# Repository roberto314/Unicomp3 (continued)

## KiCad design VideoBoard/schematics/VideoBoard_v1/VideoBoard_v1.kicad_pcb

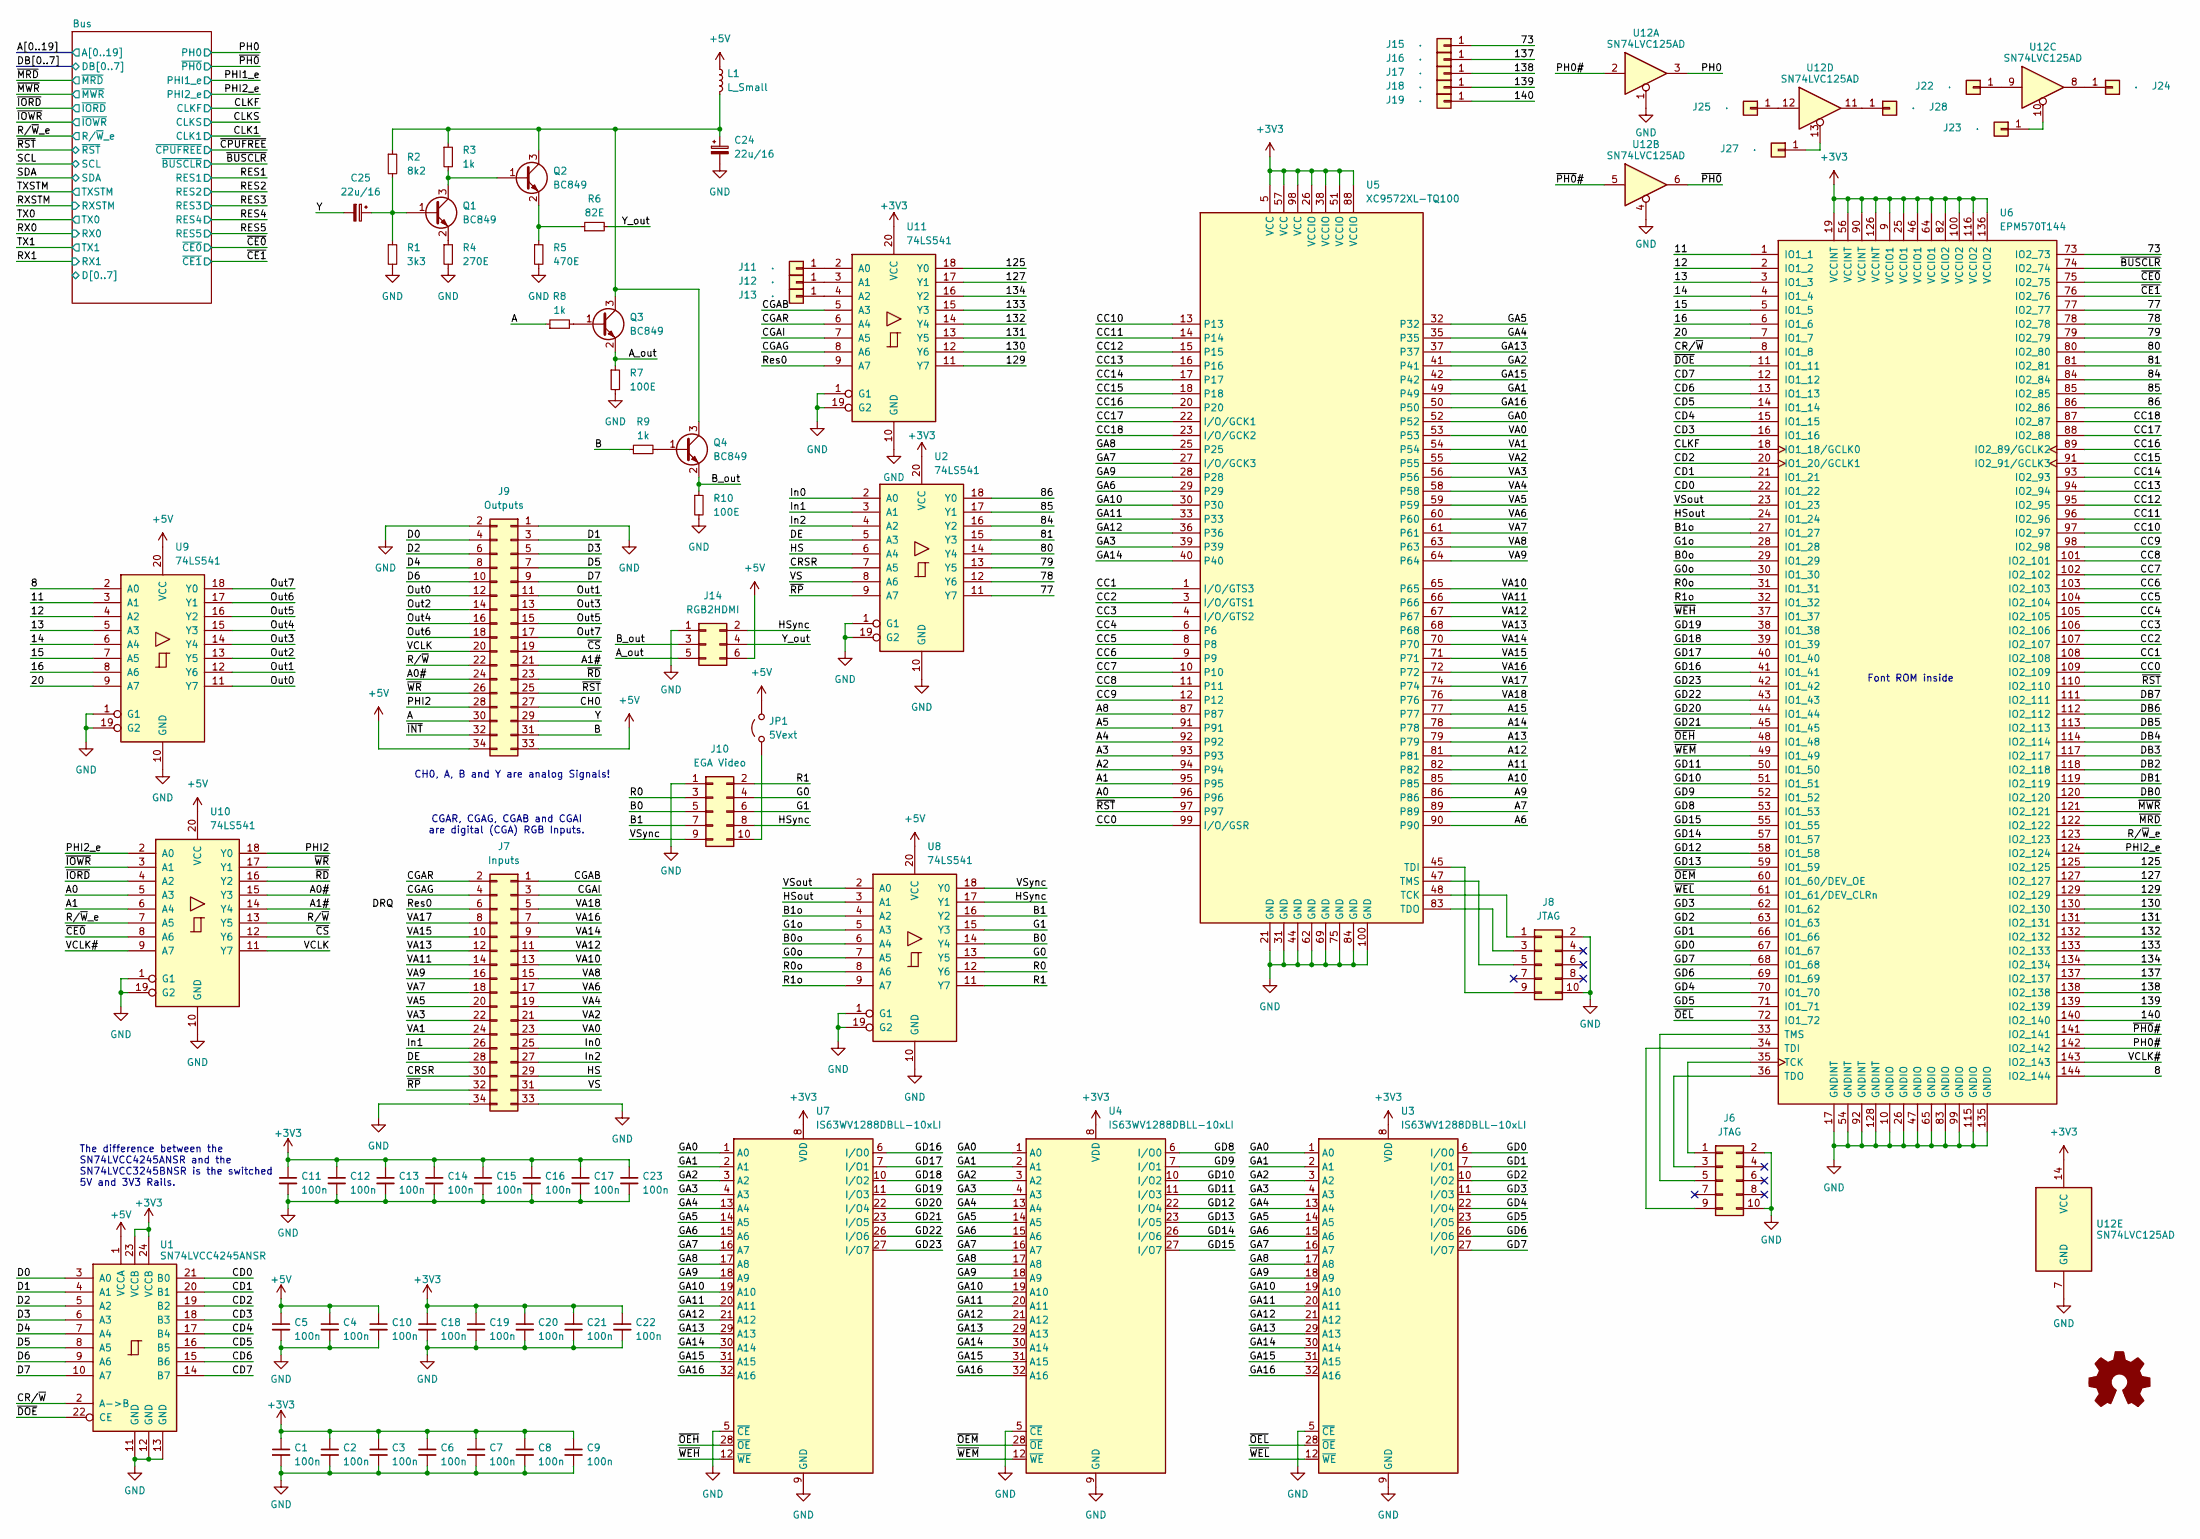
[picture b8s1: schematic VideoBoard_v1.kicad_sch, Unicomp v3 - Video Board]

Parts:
C1, C2, C3, C4, C5, C6, C7, C8, C9, C10, C11, C12, C13, C14, C15, C16, C17, C18, C19, C20, C21, C22, C23: 100n; C_0603_1608Metric_Pad1.08x0.95mm_HandSolder
C24, C25: 22u/16; CP_EIA-7343-31_Kemet-D
J6, J8: JTAG; PinHeader_2x05_P2.54mm_Horizontal
J7: Inputs; PinSocket_2x17_P2.54mm_Vertical
J9: Outputs; PinSocket_2x17_P2.54mm_Vertical
J10: EGA Video; PinHeader_2x05_P2.54mm_Horizontal
J11, J12, J13, J15, J16, J17, J18, J19, J22, J23, J24, J25, J27, J28: .; PinHeader_1x01_P1.27mm_Vertical
J14: RGB2HDMI; PinHeader_2x03_P2.54mm_Horizontal
JP1: 5Vext; PinHeader_1x02_P2.54mm_Vertical
L1: L_Small; L_1210_3225Metric_Pad1.42x2.65mm_HandSolder
Q1, Q2, Q3, Q4: BC849; SOT-23_Handsoldering
R1: 3k3; R_1206_3216Metric_Pad1.30x1.75mm_HandSolder
R2: 8k2; R_1206_3216Metric_Pad1.30x1.75mm_HandSolder
R3, R8, R9: 1k; R_1206_3216Metric_Pad1.30x1.75mm_HandSolder
R4: 270E; R_1206_3216Metric_Pad1.30x1.75mm_HandSolder
R5: 470E; R_1206_3216Metric_Pad1.30x1.75mm_HandSolder
R6: 82E; R_1206_3216Metric_Pad1.30x1.75mm_HandSolder
R7, R10: 100E; R_1206_3216Metric_Pad1.30x1.75mm_HandSolder
U1: SN74LVCC4245ANSR; SO-24_5.3x15mm_P1.27mm
U2, U8, U9, U10, U11: 74LS541; TSSOP-20_4.4x6.5mm_P0.65mm
U3, U4, U7: IS63WV1288DBLL-10xLI; TSOP-II-32_21.0x10.2mm_P1.27mm
U5: XC9572XL-TQ100; TQFP-100_14x14mm_P0.5mm
U6: EPM570T144; LQFP-144_20x20mm_P0.5mm
U12: SN74LVC125AD; SOIC-14_3.9x8.7mm_P1.27mm

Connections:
+3V3: C1.1, C2.1, C3.1, C6.1, C7.1, C8.1, C9.1, C11.1, C12.1, C13.1, C14.1, C15.1, C16.1, C17.1, C18.1, C19.1, C20.1, C21.1, C22.1, C23.1, U1.23 (VCCB), U1.24 (VCCB), U2.20 (VCC), U3.8 (VDD), U3.24 (VDD), U4.8 (VDD), U4.24 (VDD), U5.5 (VCC), U5.26 (VCCIO), U5.38 (VCCIO), U5.51 (VCCIO), U5.57 (VCC), U5.88 (VCCIO), U5.98 (VCC), U6.9 (VCCIO1), U6.19 (VCCINT), U6.25 (VCCIO1), U6.46 (VCCIO1), U6.56 (VCCINT), U6.64 (VCCIO1), U6.82 (VCCIO2), U6.90 (VCCINT), U6.100 (VCCIO2), U6.116 (VCCIO2), U6.126 (VCCINT), U6.136 (VCCIO2), U7.8 (VDD), U7.24 (VDD), U11.20 (VCC), U12.14 (VCC); also elsewhere on the board
+5V: C4.1, C5.1, C10.1, J9.33, J9.34, J14.6, JP1.2 (B), L1.1, U1.1 (VCCA), U8.20 (VCC), U9.20 (VCC), U10.20 (VCC); also elsewhere on the board
/8: U6.144 (IO2_144), U9.2 (A0)
/11: U6.1 (IO1_1), U9.3 (A1)
/12: U6.2 (IO1_2), U9.4 (A2)
/13: U6.3 (IO1_3), U9.5 (A3)
/14: U6.4 (IO1_4), U9.6 (A4)
/15: U6.5 (IO1_5), U9.7 (A5)
/16: U6.6 (IO1_6), U9.8 (A6)
/20: U6.7 (IO1_7), U9.9 (A7)
/73: J15.1, U6.73 (IO2_73)
/77: U2.11 (Y7), U6.77 (IO2_77)
/78: U2.12 (Y6), U6.78 (IO2_78)
/79: U2.13 (Y5), U6.79 (IO2_79)
/80: U2.14 (Y4), U6.80 (IO2_80)
/81: U2.15 (Y3), U6.81 (IO2_81)
/84: U2.16 (Y2), U6.84 (IO2_84)
/85: U2.17 (Y1), U6.85 (IO2_85)
/86: U2.18 (Y0), U6.86 (IO2_86)
/125: U6.125 (IO2_125), U11.18 (Y0)
/127: U6.127 (IO2_127), U11.17 (Y1)
/129: U6.129 (IO2_129), U11.11 (Y7)
/130: U6.130 (IO2_130), U11.12 (Y6)
/131: U6.131 (IO2_131), U11.13 (Y5)
/132: U6.132 (IO2_132), U11.14 (Y4)
/133: U6.133 (IO2_133), U11.15 (Y3)
/134: U6.134 (IO2_134), U11.16 (Y2)
/137: J16.1, U6.137 (IO2_137)
/138: J17.1, U6.138 (IO2_138)
/139: J18.1, U6.139 (IO2_139)
/140: J19.1, U6.140 (IO2_140)
/A: J9.30, R8.1
/A0: U5.96, U10.5 (A3); also elsewhere on the board
/A0#: J9.24, U10.15 (Y3)
/A1: U5.95, U10.6 (A4); also elsewhere on the board
/A1#: J9.21, U10.14 (Y4)
/A2: U5.94; also elsewhere on the board
/A3: U5.93; also elsewhere on the board
/A4: U5.92; also elsewhere on the board
/A5: U5.91; also elsewhere on the board
/A6: U5.90; also elsewhere on the board
/A7: U5.89; also elsewhere on the board
/A8: U5.87; also elsewhere on the board
/A9: U5.86; also elsewhere on the board
/A10: U5.85; also elsewhere on the board
/A11: U5.82; also elsewhere on the board
/A12: U5.81; also elsewhere on the board
/A13: U5.79; also elsewhere on the board
/A14: U5.78; also elsewhere on the board
/A15: U5.77; also elsewhere on the board
/A_out: J14.5, Q3.2 (E), R7.1
/B: J9.31, R9.1
/B0: J10.5, U8.14 (Y4)
/B0o: U6.29 (IO1_29), U8.6 (A4)
/B1: J10.7, U8.16 (Y2)
/B1o: U6.27 (IO1_27), U8.4 (A2)
/B_out: J14.3, Q4.2 (E), R10.1
/Bus/D0: J9.4, U1.3 (A0)
/Bus/D1: J9.3, U1.4 (A1)
/Bus/D2: J9.6, U1.5 (A2)
/Bus/D3: J9.5, U1.6 (A3)
/Bus/D4: J9.8, U1.7 (A4)
/Bus/D5: J9.7, U1.8 (A5)
/Bus/D6: J9.10, U1.9 (A6)
/Bus/D7: J9.9, U1.10 (A7)
/CC0: U5.99 (I/O/GSR), U6.109 (IO2_109)
/CC1: U5.1 (I/O/GTS3), U6.108 (IO2_108)
/CC2: U5.3 (I/O/GTS1), U6.107 (IO2_107)
/CC3: U5.4 (I/O/GTS2), U6.106 (IO2_106)
/CC4: U5.6, U6.105 (IO2_105)
/CC5: U5.8, U6.104 (IO2_104)
/CC6: U5.9, U6.103 (IO2_103)
/CC7: U5.10, U6.102 (IO2_102)
/CC8: U5.11, U6.101 (IO2_101)
/CC9: U5.12, U6.98 (IO2_98)
/CC10: U5.13, U6.97 (IO2_97)
/CC11: U5.14, U6.96 (IO2_96)
/CC12: U5.15, U6.95 (IO2_95)
/CC13: U5.16, U6.94 (IO2_94)
/CC14: U5.17, U6.93 (IO2_93)
/CC15: U5.18, U6.91 (IO2_91/GCLK3)
/CC16: U5.20, U6.89 (IO2_89/GCLK2)
/CC17: U5.22 (I/O/GCK1), U6.88 (IO2_88)
/CC18: U5.23 (I/O/GCK2), U6.87 (IO2_87)
/CD0: U1.21 (B0), U6.22 (IO1_22)
/CD1: U1.20 (B1), U6.21 (IO1_21)
/CD2: U1.19 (B2), U6.20 (IO1_20/GCLK1)
/CD3: U1.18 (B3), U6.16 (IO1_16)
/CD4: U1.17 (B4), U6.15 (IO1_15)
/CD5: U1.16 (B5), U6.14 (IO1_14)
/CD6: U1.15 (B6), U6.13 (IO1_13)
/CD7: U1.14 (B7), U6.12 (IO1_12)
/CGAB: J7.1, U11.5 (A3)
/CGAG: J7.4, U11.8 (A6)
/CGAI: J7.3, U11.7 (A5)
/CGAR: J7.2, U11.6 (A4)
/CH0: J9.27
/CLKF: U6.18 (IO1_18/GCLK0); also elsewhere on the board
/CRSR: J7.30, U2.7 (A5)
/CR/~W: U1.2 (A->B), U6.8 (IO1_8)
/DB0: U6.120 (IO2_120); also elsewhere on the board
/DB1: U6.119 (IO2_119); also elsewhere on the board
/DB2: U6.118 (IO2_118); also elsewhere on the board
/DB3: U6.117 (IO2_117); also elsewhere on the board
/DB4: U6.114 (IO2_114); also elsewhere on the board
/DB5: U6.113 (IO2_113); also elsewhere on the board
/DB6: U6.112 (IO2_112); also elsewhere on the board
/DB7: U6.111 (IO2_111); also elsewhere on the board
/DE: J7.28, U2.5 (A3)
/G0: J10.4, U8.13 (Y5)
/G0o: U6.30 (IO1_30), U8.7 (A5)
/G1: J10.6, U8.15 (Y3)
/G1o: U6.28 (IO1_28), U8.5 (A3)
/GA0: U3.1 (A0), U4.1 (A0), U5.52, U7.1 (A0)
/GA1: U3.2 (A1), U4.2 (A1), U5.49, U7.2 (A1)
/GA2: U3.3 (A2), U4.3 (A2), U5.41, U7.3 (A2)
/GA3: U3.4 (A3), U4.4 (A3), U5.39, U7.4 (A3)
/GA4: U3.13 (A4), U4.13 (A4), U5.35, U7.13 (A4)
/GA5: U3.14 (A5), U4.14 (A5), U5.32, U7.14 (A5)
/GA6: U3.15 (A6), U4.15 (A6), U5.29, U7.15 (A6)
/GA7: U3.16 (A7), U4.16 (A7), U5.27 (I/O/GCK3), U7.16 (A7)
/GA8: U3.17 (A8), U4.17 (A8), U5.25, U7.17 (A8)
/GA9: U3.18 (A9), U4.18 (A9), U5.28, U7.18 (A9)
/GA10: U3.19 (A10), U4.19 (A10), U5.30, U7.19 (A10)
/GA11: U3.20 (A11), U4.20 (A11), U5.33, U7.20 (A11)
/GA12: U3.21 (A12), U4.21 (A12), U5.36, U7.21 (A12)
/GA13: U3.29 (A13), U4.29 (A13), U5.37, U7.29 (A13)
/GA14: U3.30 (A14), U4.30 (A14), U5.40, U7.30 (A14)
/GA15: U3.31 (A15), U4.31 (A15), U5.42, U7.31 (A15)
/GA16: U3.32 (A16), U4.32 (A16), U5.50, U7.32 (A16)
/GD0: U3.6 (I/O0), U6.67 (IO1_67)
/GD1: U3.7 (I/O1), U6.66 (IO1_66)
/GD2: U3.10 (I/O2), U6.63 (IO1_63)
/GD3: U3.11 (I/O3), U6.62 (IO1_62)
/GD4: U3.22 (I/O4), U6.70 (IO1_70)
/GD5: U3.23 (I/O5), U6.71 (IO1_71)
/GD6: U3.26 (I/O6), U6.69 (IO1_69)
/GD7: U3.27 (I/O7), U6.68 (IO1_68)
/GD8: U4.6 (I/O0), U6.53 (IO1_53)
/GD9: U4.7 (I/O1), U6.52 (IO1_52)
/GD10: U4.10 (I/O2), U6.51 (IO1_51)
/GD11: U4.11 (I/O3), U6.50 (IO1_50)
/GD12: U4.22 (I/O4), U6.58 (IO1_58)
/GD13: U4.23 (I/O5), U6.59 (IO1_59)
/GD14: U4.26 (I/O6), U6.57 (IO1_57)
/GD15: U4.27 (I/O7), U6.55 (IO1_55)
/GD16: U6.41 (IO1_41), U7.6 (I/O0)
/GD17: U6.40 (IO1_40), U7.7 (I/O1)
/GD18: U6.39 (IO1_39), U7.10 (I/O2)
/GD19: U6.38 (IO1_38), U7.11 (I/O3)
/GD20: U6.44 (IO1_44), U7.22 (I/O4)
/GD21: U6.45 (IO1_45), U7.23 (I/O5)
/GD22: U6.43 (IO1_43), U7.26 (I/O6)
/GD23: U6.42 (IO1_42), U7.27 (I/O7)
/HS: J7.29, U2.6 (A4)
/HSout: U6.24 (IO1_24), U8.3 (A1)
/HSync: J10.8, J14.2, U8.17 (Y1)
/In0: J7.25, U2.2 (A0)
/In1: J7.26, U2.3 (A1)
/In2: J7.27, U2.4 (A2)
/Out0: J9.12, U9.11 (Y7)
/Out1: J9.11, U9.12 (Y6)
/Out2: J9.14, U9.13 (Y5)
/Out3: J9.13, U9.14 (Y4)
/Out4: J9.16, U9.15 (Y3)
/Out5: J9.15, U9.16 (Y2)
/Out6: J9.18, U9.17 (Y1)
/Out7: J9.17, U9.18 (Y0)
/PH0: U12.3; also elsewhere on the board
/PH0#: U6.142 (IO2_142), U12.2
/PHI2: J9.28, U10.18 (Y0)
/PHI2_e: U6.124 (IO2_124), U10.2 (A0); also elsewhere on the board
/R0: J10.3, U8.12 (Y6)
/R0o: U6.31 (IO1_31), U8.8 (A6)
/R1: J10.2, U8.11 (Y7)
/R1o: U6.32 (IO1_32), U8.9 (A7)
/Res0: J7.6, U11.9 (A7)
/R/~W: J9.22, U10.13 (Y5)
/R/~W_e: U6.123 (IO2_123), U10.7 (A5); also elsewhere on the board
/VA0: J7.23, U5.53
/VA1: J7.24, U5.54
/VA2: J7.21, U5.55
/VA3: J7.22, U5.56
/VA4: J7.19, U5.58
/VA5: J7.20, U5.59
/VA6: J7.17, U5.60
/VA7: J7.18, U5.61
/VA8: J7.15, U5.63
/VA9: J7.16, U5.64
/VA10: J7.13, U5.65
/VA11: J7.14, U5.66
/VA12: J7.11, U5.67
/VA13: J7.12, U5.68
/VA14: J7.9, U5.70
/VA15: J7.10, U5.71
/VA16: J7.7, U5.72
/VA17: J7.8, U5.74
/VA18: J7.5, U5.76
/VCLK: J9.20, U10.11 (Y7)
/VCLK#: U6.143 (IO2_143), U10.9 (A7)
/VS: J7.31, U2.8 (A6)
/VSout: U6.23 (IO1_23), U8.2 (A0)
/VSync: J10.9, U8.18 (Y0)
/Y: C25.2, J9.29
/Y_out: J14.4, R6.2
/~BUSCLR: U6.74 (IO2_74); also elsewhere on the board
/~CE0: U6.75 (IO2_75), U10.8 (A6); also elsewhere on the board
/~CE1: U6.76 (IO2_76); also elsewhere on the board
/~CS: J9.19, U10.12 (Y6)
/~DOE: U1.22 (CE), U6.11 (IO1_11)
/~INT: J9.32
/~IORD: U10.4 (A2); also elsewhere on the board
/~IOWR: U10.3 (A1); also elsewhere on the board
/~MRD: U6.122 (IO2_122); also elsewhere on the board
/~MWR: U6.121 (IO2_121); also elsewhere on the board
/~OEH: U6.48 (IO1_48), U7.28 (~OE)
/~OEL: U3.28 (~OE), U6.72 (IO1_72)
/~OEM: U4.28 (~OE), U6.60 (IO1_60/DEV_OE)
/~PH0: U12.6; also elsewhere on the board
/~PH0#: U6.141 (IO2_141), U12.5
/~RD: J9.23, U10.16 (Y2)
/~RP: J7.32, U2.9 (A7)
/~RST: J9.25, U5.97, U6.110 (IO2_110); also elsewhere on the board
/~WEH: U6.37 (IO1_37), U7.12 (~WE)
/~WEL: U3.12 (~WE), U6.61 (IO1_61/DEV_CLRn)
/~WEM: U4.12 (~WE), U6.49 (IO1_49)
/~WR: J9.26, U10.17 (Y1)
GND: C1.2, C2.2, C3.2, C4.2, C5.2, C6.2, C7.2, C8.2, C9.2, C10.2, C11.2, C12.2, C13.2, C14.2, C15.2, C16.2, C17.2, C18.2, C19.2, C20.2, C21.2, C22.2, C23.2, C24.2, J6.2, J6.10, J7.33, J7.34, J8.2, J8.10, J9.1, J9.2, J10.1, J14.1, R1.2, R4.2, R5.2, R7.2, R10.2, U1.11 (GND), U1.12 (GND), U1.13 (GND), U2.1 (G1), U2.10 (GND), U2.19 (G2), U3.5 (~CE), U3.9 (GND), U3.25 (GND), U4.5 (~CE), U4.9 (GND), U4.25 (GND), U5.21 (GND), U5.31 (GND), U5.44 (GND), U5.62 (GND), U5.69 (GND), U5.75 (GND), U5.84 (GND), U5.100 (GND), U6.10 (GNDIO), U6.17 (GNDINT), U6.26 (GNDIO), U6.47 (GNDIO), U6.54 (GNDINT), U6.65 (GNDIO), U6.83 (GNDIO), U6.92 (GNDINT), U6.99 (GNDIO), U6.115 (GNDIO), U6.128 (GNDINT), U6.135 (GNDIO), U7.5 (~CE), U7.9 (GND), U7.25 (GND), U8.1 (G1), U8.10 (GND), U8.19 (G2), U9.1 (G1), U9.10 (GND), U9.19 (G2), U10.1 (G1), U10.10 (GND), U10.19 (G2), U11.1 (G1), U11.10 (GND), U11.19 (G2), U12.1, U12.4, U12.7 (GND); also elsewhere on the board
unnamed: J6.1, U6.35 (TCK)
unnamed: J6.3, U6.36 (TDO)
unnamed: J6.5, U6.33 (TMS)
unnamed: J6.9, U6.34 (TDI)
unnamed: J8.1, U5.48 (TCK)
unnamed: J8.3, U5.83 (TDO)
unnamed: J8.5, U5.47 (TMS)
unnamed: J8.9, U5.45 (TDI)
unnamed: J10.10, JP1.1 (A)
unnamed: J11.1, U11.2 (A0)
unnamed: J12.1, U11.3 (A1)
unnamed: J13.1, U11.4 (A2)
unnamed: J22.1, U12.9
unnamed: J23.1, U12.10
unnamed: J24.1, U12.8
unnamed: J25.1, U12.12
unnamed: J27.1, U12.13
unnamed: J28.1, U12.11
unnamed: C25.1, Q1.1 (B), R1.1, R2.2
unnamed: Q1.3 (C), Q2.1 (B), R3.2
unnamed: Q1.2 (E), R4.1
unnamed: C24.1, L1.2, Q2.3 (C), Q3.3 (C), Q4.3 (C), R2.1, R3.1
unnamed: Q2.2 (E), R5.1, R6.1
unnamed: Q3.1 (B), R8.2
unnamed: Q4.1 (B), R9.2

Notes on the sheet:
CGAR, CGAG, CGAB and CGAI are digital (CGA) RGB Inputs.
The difference between the SN74LVCC4245ANSR and the SN74LVCC3245BNSR is the switched 5V and 3V3 Rails.
CH0, A, B and Y are analog Signals!
Font ROM inside

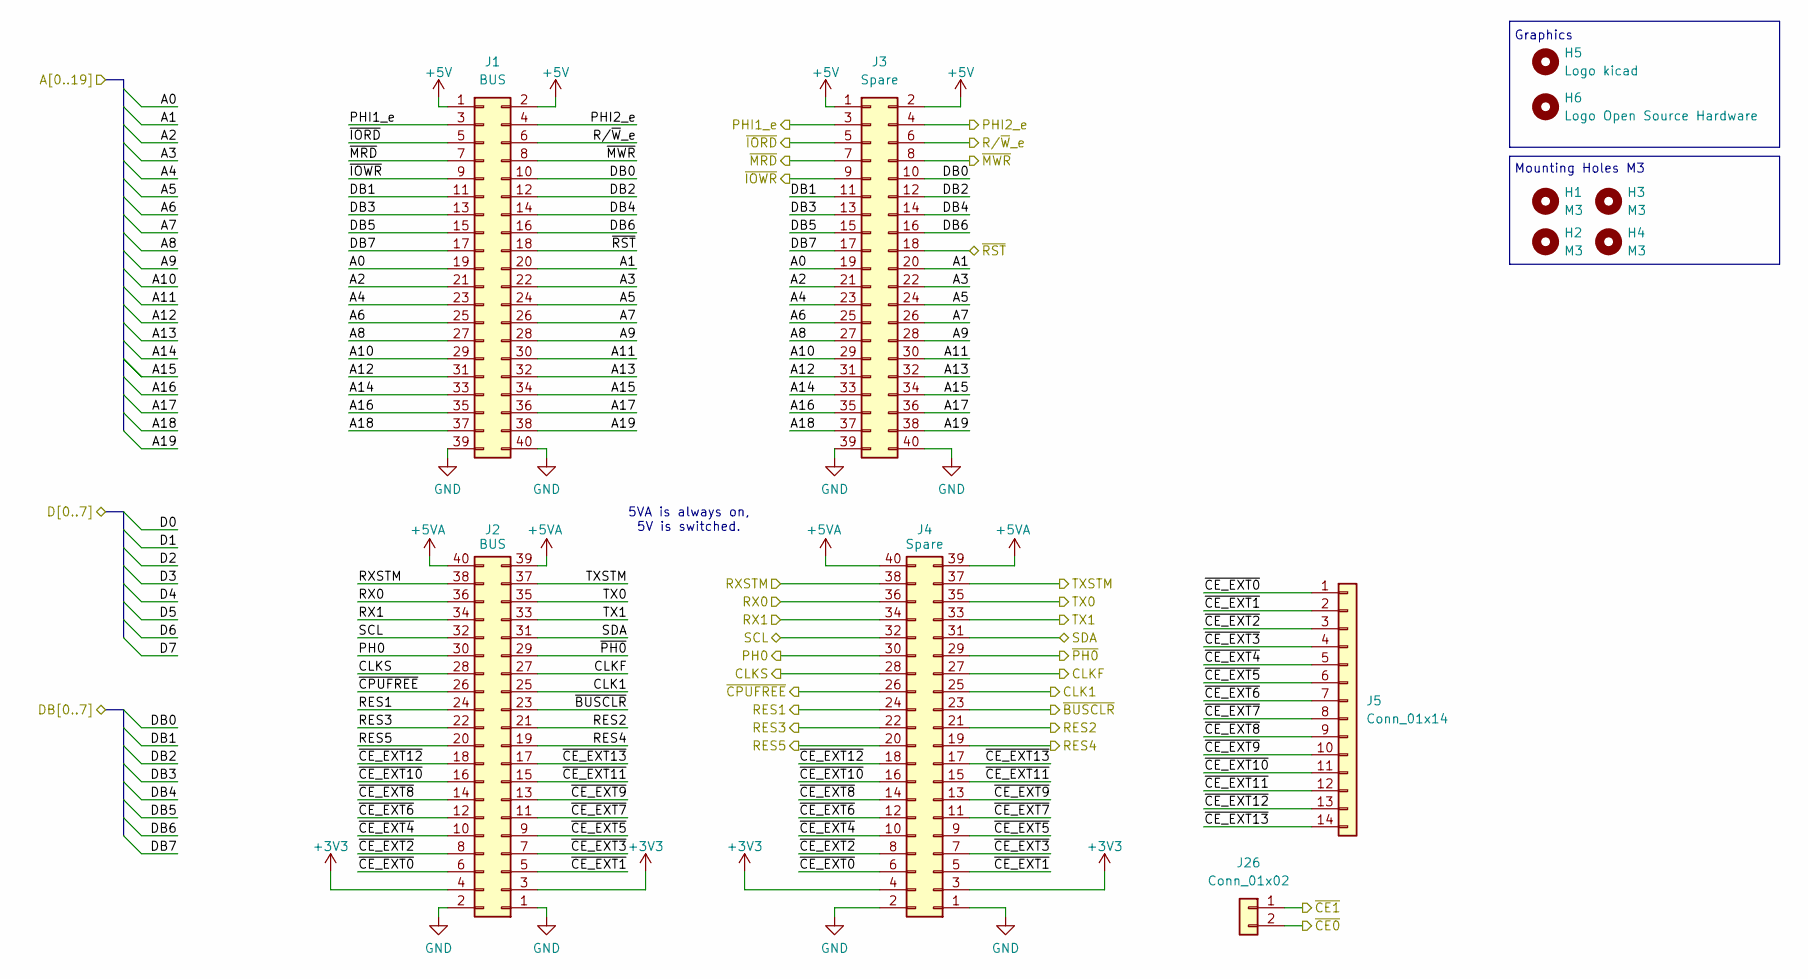
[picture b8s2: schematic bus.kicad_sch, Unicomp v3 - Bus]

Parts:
H1, H2, H3, H4: M3; MountingHole_3.2mm_M3
H5: Logo kicad; KiCad-Logo2_6mm_SilkScreen
H6: Logo Open Source Hardware; OSHW-Logo2_7.3x6mm_SilkScreen
J1, J2: BUS; PinSocket_2x20_P2.54mm_Vertical
J3, J4: Spare; PinSocket_2x20_P2.54mm_Vertical
J5: Conn_01x14; PinSocket_1x14_P2.54mm_Vertical
J26: Conn_01x02; PinSocket_1x02_P2.54mm_Vertical

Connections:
+3V3: J2.3, J2.4, J4.3, J4.4; also elsewhere on the board
+5V: J1.1, J1.2, J3.1, J3.2; also elsewhere on the board
+5VA: J2.39, J2.40, J4.39, J4.40
/A0: J1.19, J3.19; also elsewhere on the board
/A1: J1.20, J3.20; also elsewhere on the board
/A2: J1.21, J3.21; also elsewhere on the board
/A3: J1.22, J3.22; also elsewhere on the board
/A4: J1.23, J3.23; also elsewhere on the board
/A5: J1.24, J3.24; also elsewhere on the board
/A6: J1.25, J3.25; also elsewhere on the board
/A7: J1.26, J3.26; also elsewhere on the board
/A8: J1.27, J3.27; also elsewhere on the board
/A9: J1.28, J3.28; also elsewhere on the board
/A10: J1.29, J3.29; also elsewhere on the board
/A11: J1.30, J3.30; also elsewhere on the board
/A12: J1.31, J3.31; also elsewhere on the board
/A13: J1.32, J3.32; also elsewhere on the board
/A14: J1.33, J3.33; also elsewhere on the board
/A15: J1.34, J3.34; also elsewhere on the board
/A16: J1.35, J3.35
/A17: J1.36, J3.36
/A18: J1.37, J3.37
/A19: J1.38, J3.38
/Bus/~CE_EXT0: J2.6, J4.6, J5.1
/Bus/~CE_EXT1: J2.5, J4.5, J5.2
/Bus/~CE_EXT2: J2.8, J4.8, J5.3
/Bus/~CE_EXT3: J2.7, J4.7, J5.4
/Bus/~CE_EXT4: J2.10, J4.10, J5.5
/Bus/~CE_EXT5: J2.9, J4.9, J5.6
/Bus/~CE_EXT6: J2.12, J4.12, J5.7
/Bus/~CE_EXT7: J2.11, J4.11, J5.8
/Bus/~CE_EXT8: J2.14, J4.14, J5.9
/Bus/~CE_EXT9: J2.13, J4.13, J5.10
/Bus/~CE_EXT10: J2.16, J4.16, J5.11
/Bus/~CE_EXT11: J2.15, J4.15, J5.12
/Bus/~CE_EXT12: J2.18, J4.18, J5.13
/Bus/~CE_EXT13: J2.17, J4.17, J5.14
/CLK1: J2.25, J4.25
/CLKF: J2.27, J4.27; also elsewhere on the board
/CLKS: J2.28, J4.28
/DB0: J1.10, J3.10; also elsewhere on the board
/DB1: J1.11, J3.11; also elsewhere on the board
/DB2: J1.12, J3.12; also elsewhere on the board
/DB3: J1.13, J3.13; also elsewhere on the board
/DB4: J1.14, J3.14; also elsewhere on the board
/DB5: J1.15, J3.15; also elsewhere on the board
/DB6: J1.16, J3.16; also elsewhere on the board
/DB7: J1.17, J3.17; also elsewhere on the board
/PH0: J2.30, J4.30; also elsewhere on the board
/PHI1_e: J1.3, J3.3
/PHI2_e: J1.4, J3.4; also elsewhere on the board
/RES1: J2.24, J4.24
/RES2: J2.21, J4.21
/RES3: J2.22, J4.22
/RES4: J2.19, J4.19
/RES5: J2.20, J4.20
/RX0: J2.36, J4.36
/RX1: J2.34, J4.34
/RXSTM: J2.38, J4.38
/R/~W_e: J1.6, J3.6; also elsewhere on the board
/SCL: J2.32, J4.32
/SDA: J2.31, J4.31
/TX0: J2.35, J4.35
/TX1: J2.33, J4.33
/TXSTM: J2.37, J4.37
/~BUSCLR: J2.23, J4.23; also elsewhere on the board
/~CE0: J26.2; also elsewhere on the board
/~CE1: J26.1; also elsewhere on the board
/~CPUFREE: J2.26, J4.26
/~IORD: J1.5, J3.5; also elsewhere on the board
/~IOWR: J1.9, J3.9; also elsewhere on the board
/~MRD: J1.7, J3.7; also elsewhere on the board
/~MWR: J1.8, J3.8; also elsewhere on the board
/~PH0: J2.29, J4.29; also elsewhere on the board
/~RST: J1.18, J3.18; also elsewhere on the board
GND: J1.39, J1.40, J2.1, J2.2, J3.39, J3.40, J4.1, J4.2; also elsewhere on the board

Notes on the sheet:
Graphics
5VA is always on, 5V is switched.
Mounting Holes M3

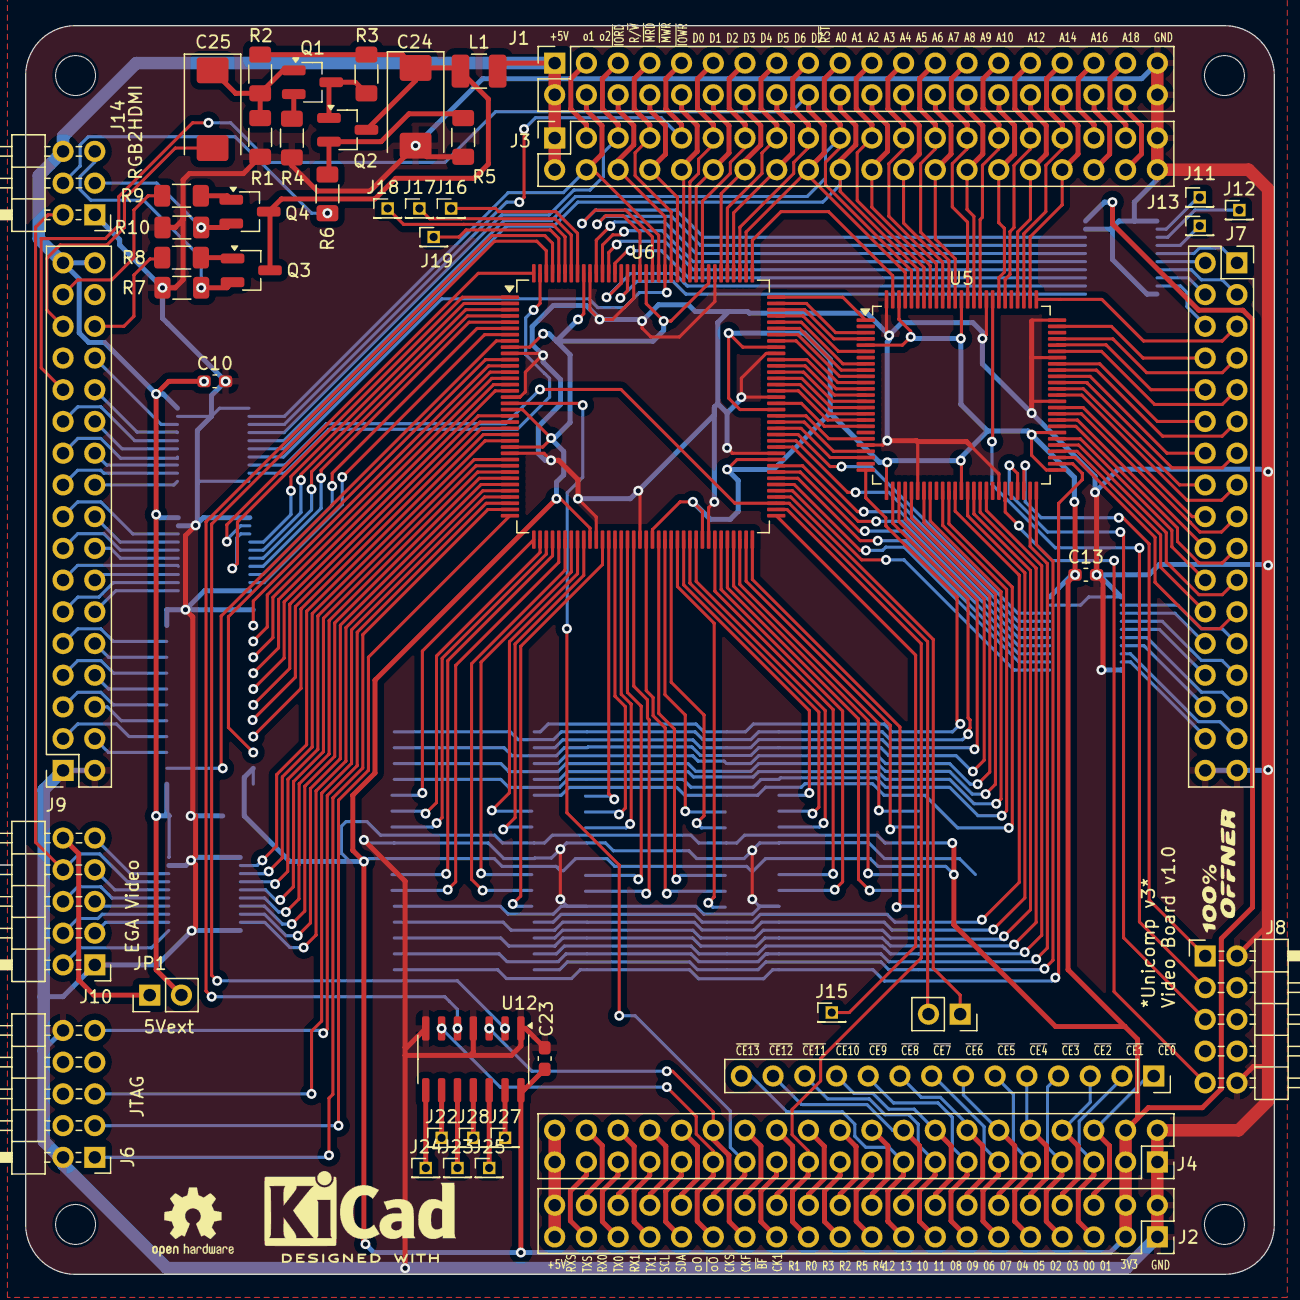
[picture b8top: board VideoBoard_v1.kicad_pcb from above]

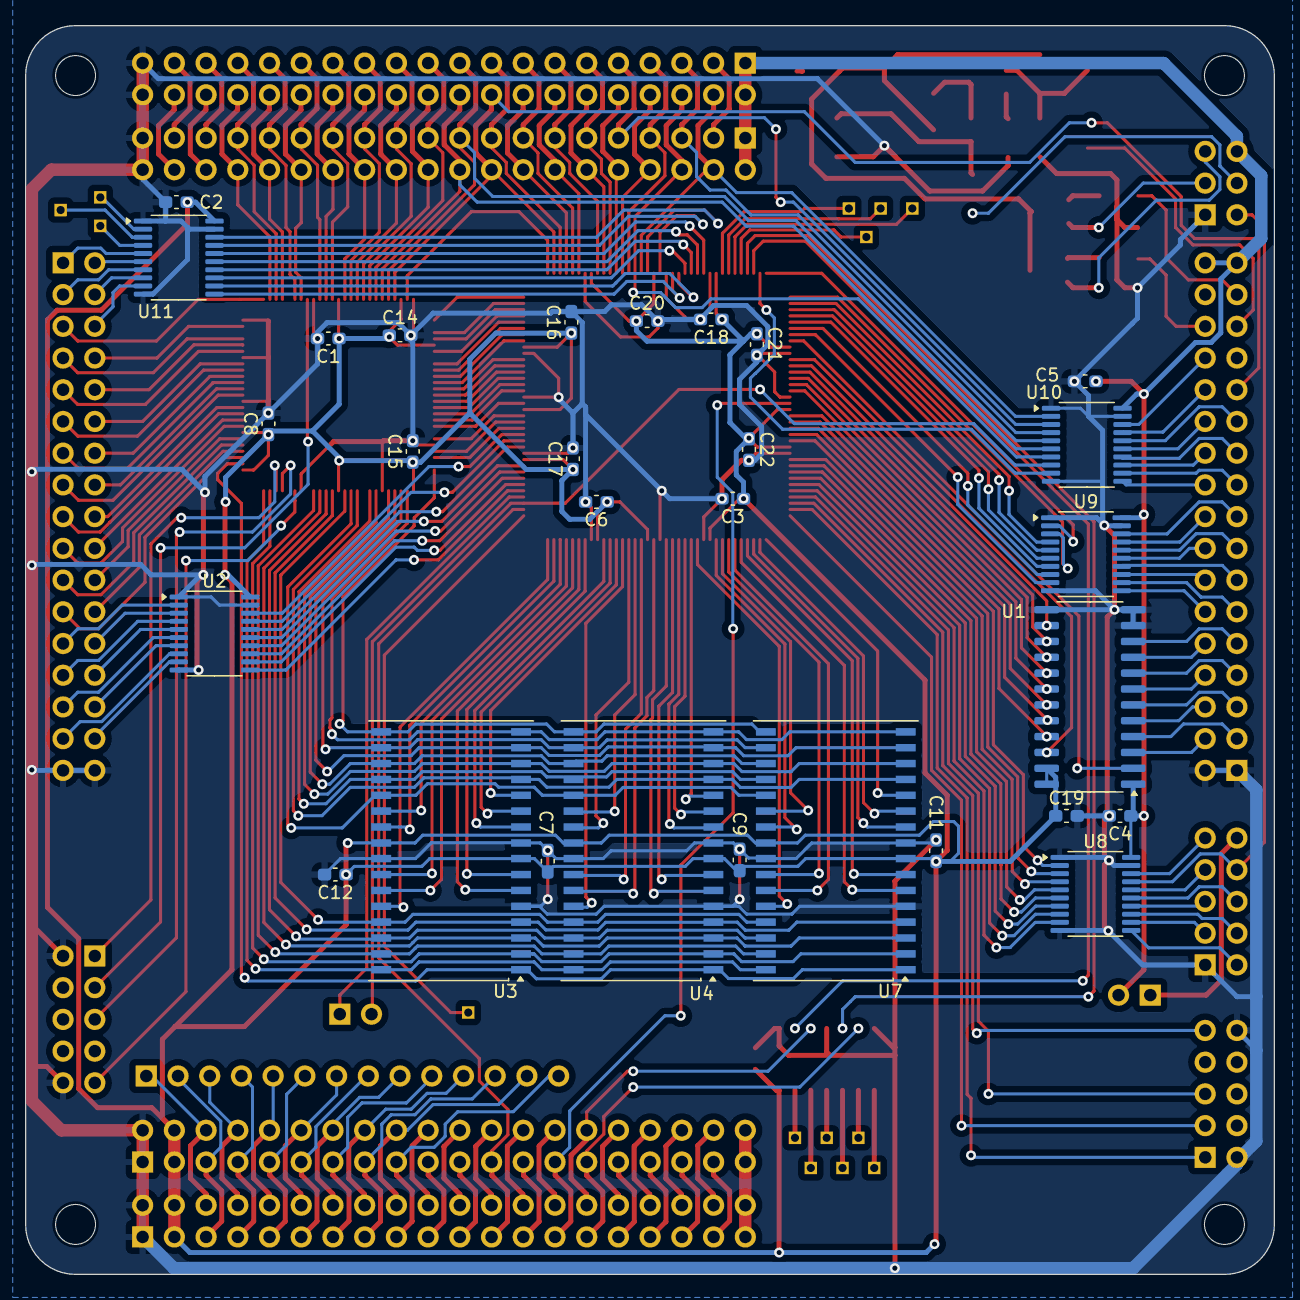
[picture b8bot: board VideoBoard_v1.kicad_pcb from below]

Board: 2 copper layers, 100.0 x 100.0 mm, 85 parts (29 on the bottom side), 287 nets.

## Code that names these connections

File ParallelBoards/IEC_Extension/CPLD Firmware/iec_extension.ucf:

NET "CNT"       LOC = "p39"  ;
NET "SP"        LOC = "p40"  ;
NET "_128_64"   LOC = "p41"  ;
NET "RST_drv"   LOC = "p42"  ;
NET "P43"       LOC = "p43"  ;
NET "P44"       LOC = "p44"  ;
NET "P1"        LOC = "p1"  ;
NET "RST_in"    LOC = "p2"  ;--
NET "ATN_out"   LOC = "p3"  ;--
#-----------------------------
NET "RST_out"   LOC = "p5"  ;--
NET "FCLK_out"  LOC = "p6"  ;--
NET "SCLK_out"  LOC = "p7"  ;--
NET "SDAT_out"  LOC = "p8"  ;--
NET "SDAT_in"   LOC = "p12"  ;--
NET "FCLK_in"   LOC = "p13"  ;--
NET "SCLK_in"   LOC = "p14"  ;--
NET "ATN_in"    LOC = "p16"  ;--
NET "Fout_Fin"  LOC = "p18"  ;
#-----------------------------
NET "SCLK_sens" LOC = "p19"  ;
NET "SCLK_drv"  LOC = "p20"  ;
NET "SDAT_sens" LOC = "p21"  ;
NET "SDAT_drv"  LOC = "p22"  ;
NET "ATN_sens"  LOC = "p23"  ;
NET "ATN_drv"   LOC = "p27"  ;
NET "P28"       LOC = "p28"  ;
#-----------------------------
NET "P29"       LOC = "p29"  ;
NET "P30"       LOC = "p30"  ;
NET "P31"       LOC = "p31"  ;
NET "P32"       LOC = "p32"  ;
NET "P33"       LOC = "p33"  ;
NET "P34"       LOC = "p34"  ;
NET "P36"       LOC = "p36"  ;
NET "P37"       LOC = "p37"  ;
NET "P38"       LOC = "p38"  ;

# ; NET "GND" LOC = "p4"  ;
# ; NET "TDI" LOC = "p9"  ;
# ; NET "TMS" LOC = "p10" ;
# ; NET "TCK" LOC = "p11" ;
# ; NET "VCC" LOC = "p15" ;
# ; NET "GND" LOC = "p17" ;
# ; NET "TDO" LOC = "p24" ;
# ; NET "GND" LOC = "p25" ;
# ; NET "VCC" LOC = "p26" ;
# ; NET "VCC" LOC = "p35" ;

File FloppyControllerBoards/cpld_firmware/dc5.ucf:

NET "nNMI"     LOC = "p1"  ;
NET "nINT"     LOC = "p2"  ;
NET "nDSKRDY"  LOC = "p3"  ;
NET "nDSEN"    LOC = "p5"  ;
NET "DSA"      LOC = "p6"  ;
NET "DSB"      LOC = "p7"  ;
NET "nSIDE1"   LOC = "p8"  ;
NET "MOTCP"    LOC = "p12"  ;
NET "nDSKCHG"  LOC = "p13"  ;
NET "nINTRQ"   LOC = "p14"  ;
NET "DRQ"      LOC = "p16"  ;
NET "nDDEN"    LOC = "p18"  ;
NET "nWG"      LOC = "p19"  ;
NET "MOTFDC"   LOC = "p20"  ;
NET "CLK1"     LOC = "p21"  ;
NET "HLT"      LOC = "p22"  ;
NET "FDCCLK"   LOC = "p23"  ;
NET "nCE0"     LOC = "p27"  ;
NET "RW"       LOC = "p28"  ;
NET "D[7]"     LOC = "p29"  ;
NET "D[6]"     LOC = "p30"  ;
NET "D[5]"     LOC = "p31"  ;
NET "D[4]"     LOC = "p32"  ;
NET "D[3]"     LOC = "p33"  ;
NET "D[2]"     LOC = "p34"  ;
NET "D[1]"     LOC = "p36"  ;
NET "D[0]"     LOC = "p37"  ;
NET "E"        LOC = "p38"  ;
NET "A3"       LOC = "p39"  ;
NET "nRST"     LOC = "p40"  ;
NET "HLD"      LOC = "p41"  ;
NET "nDOE"     LOC = "p42"  ;
NET "CLK8M"    LOC = "p43"  ;
NET "SSO"      LOC = "p44"  ;

# ; NET "GND" LOC = "p4"  ;
# ; NET "TDI" LOC = "p9"  ;
# ; NET "TMS" LOC = "p10" ;
# ; NET "TCK" LOC = "p11" ;
# ; NET "VCC" LOC = "p15" ;
# ; NET "GND" LOC = "p17" ;
# ; NET "TDO" LOC = "p24" ;
# ; NET "GND" LOC = "p25" ;
# ; NET "VCC" LOC = "p26" ;
# ; NET "VCC" LOC = "p35" ;

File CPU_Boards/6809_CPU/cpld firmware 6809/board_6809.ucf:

NET "PH0"      LOC = "p1"  ;
NET "nPH0"     LOC = "p2"  ;
NET "CLKF"     LOC = "p3"  ;
NET "nDOE"     LOC = "p31"  ;
NET "nAOE"     LOC = "p32"  ;
NET "nMWR"     LOC = "p33"  ;
NET "nMRD"     LOC = "p34"  ;
NET "RnW"      LOC = "p36"  ;
NET "E_C"      LOC = "p37"  ;
NET "Q_C"      LOC = "p38"  ;
NET "CLKCPU"   LOC = "p39"  ;
NET "nBUSFREE" LOC = "p43"  ;
NET "BA"       LOC = "p44"  ;
NET "nRST"     LOC = "p42"  ;

NET "A[0]"   LOC = "p30"  ;
NET "A[1]"   LOC = "p29"  ;
NET "A[2]"  LOC = "p28"  ;
NET "A[3]"  LOC = "p27"  ;
NET "A[4]"  LOC = "p23"  ;
NET "A[5]"  LOC = "p22"  ;
NET "A[6]"  LOC = "p21"  ;
NET "A[7]"  LOC = "p20"  ;
NET "A[8]"   LOC = "p19"  ;
NET "A[9]"   LOC = "p18"  ;
NET "A[10]"  LOC = "p16"  ;
NET "A[11]"  LOC = "p14"  ;
NET "A[12]"  LOC = "p13"  ;
NET "A[13]"  LOC = "p12"  ;
NET "A[14]"  LOC = "p8"  ;
NET "A[15]"  LOC = "p7"  ;

NET "RES0"  LOC = "p40"  ;
NET "RES1"  LOC = "p41"  ;

# ; NET "GND" LOC = "p4"  ;
# ; NET "TDI" LOC = "p9"  ;
# ; NET "TMS" LOC = "p10" ;
# ; NET "TCK" LOC = "p11" ;
# ; NET "VCC" LOC = "p15" ;
# ; NET "GND" LOC = "p17" ;
# ; NET "TDO" LOC = "p24" ;
# ; NET "GND" LOC = "p25" ;
# ; NET "VCC" LOC = "p26" ;
# ; NET "VCC" LOC = "p35" ;

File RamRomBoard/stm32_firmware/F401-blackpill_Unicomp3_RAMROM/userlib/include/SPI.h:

/*
 * SPI.h
 *
 *  Created on: Nov 19, 2022
 *      Author: rob
 */

#ifndef USERLIB_INCLUDE_SPI_H_
#define USERLIB_INCLUDE_SPI_H_

#include "ch.h"
#include "hal.h"

//typedef union {
//  uint32_t _32;
//  struct _8{
//    uint8_t _8l;
//    uint8_t _8lm;
//    uint8_t _8hm;
//    uint8_t _8h;
//  };
//}u_cv_t;

//typedef struct {
//    union {
//      uint32_t _32;
//      struct {
//        uint8_t _8l;
//        uint8_t _8lm;
//        uint8_t _8hm;
//        uint8_t _8h;
//      };
//    };
//  uint8_t cs;
//  uint8_t mask;
//} st_configdata_t;

#define SPI_DRIVER   (&SPID1)
#define SPI_PORT     GPIOA
#define SCK_PAD      5  //PA5
#define MISO_PAD     6  //PA6
#define MOSI_PAD     7  //PA7
//#define CS_PORT      GPIOC
//#define CS_PAD       4

#define DEBUG         PAL_LINE(GPIOC, 15U) // Is JTAG Clock
#define LED           PAL_LINE(GPIOC, 13U) // Is JTAG Clock

#define PLD           PAL_LINE(GPIOA, 1U)  // Low: Load into Shift register
#define RAMCE         PAL_LINE(GPIOA, 4U)  // Low: RAM Chip Enable
#define EXTRST        PAL_LINE(GPIOA, 10U) // External reset
#define CPC           PAL_LINE(GPIOA, 15U) // Counter Tic

#define CERAMWR       PAL_LINE(GPIOB, 0U)
#define RAMWR         PAL_LINE(GPIOB, 1U)  // RAM Writepulse
#define DATOE         PAL_LINE(GPIOB, 2U)  // RAM Output Enable
#define MRC           PAL_LINE(GPIOB, 3U)  // Counter Reset - Low Active
#define CNTOE         PAL_LINE(GPIOB, 5U)   // Counter Output Enable - Low Active
#define BUSFREE       PAL_LINE(GPIOB, 9U)  // Low if Bus is High-Z - Input
#define TRESET        PAL_LINE(GPIOB, 10U) // Target Reset - High active

#define DEBUG_HI  palSetLine(DEBUG)
#define DEBUG_LOW palClearLine(DEBUG)
#define LED_OFF  palSetLine(LED)
#define LED_ON palClearLine(LED)
#define RAM_ACTIVE palClearLine(RAMCE)
#define RAM_INACTIVE palSetLine(RAMCE)
#define PLD_IDLE palSetLine(PLD)
#define PLD_LOAD palClearLine(PLD)
#define CPC_HIGH palSetLine(CPC)
#define CPC_LOW palClearLine(CPC)
#define CEWR_INACTIVE palSetLine(CERAMWR)
#define CEWR_ACTIVE palClearLine(CERAMWR)
#define WE_INACTIVE palSetLine(RAMWR)
#define WE_ACTIVE palClearLine(RAMWR)
#define DATOE_ACTIVE palClearLine(DATOE)
#define DATOE_INACTIVE palSetLine(DATOE)
#define MRC_INACTIVE palSetLine(MRC)
#define MRC_ACTIVE palClearLine(MRC)
#define CNTOE_INACTIVE palSetLine(CNTOE)
#define CNTOE_ACTIVE palClearLine(CNTOE)
#define TRESET_ACTIVE palClearLine(TRESET)
#define TRESET_INACTIVE palSetLine(TRESET)

void SPI_init(void);
//void WriteSPI(int32_t val);
void write_single_byte(uint8_t data, int32_t address, uint8_t reset);
uint8_t read_single_byte(int32_t address, uint8_t reset);
uint8_t read_next_byte(void);
void write_next_byte(uint8_t data);
void read_block(int32_t address, int32_t len, uint8_t * data, uint8_t reset);
void write_block(int32_t address, int32_t len, uint8_t * data, uint8_t reset);
void write_block_no_setup(int32_t len, uint8_t * data, uint8_t reset);
void write_config(uint8_t *buf, uint32_t size);
void write_pins(uint8_t data);

#endif /* USERLIB_INCLUDE_SPI_H_ */

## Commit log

2024-05-27 Initial
2024-05-27 Readme update
2024-05-28 CPLD Example Files added
2024-05-28 Datasheets added
2024-05-29 cpld examples update
2024-06-10 New XC9572 Example
2024-09-26 Schematics of RAMROM Board updated
2024-09-26 Readme updated
2024-09-30 Diodes on Databus added, DS1314 different footprint
2024-10-12 many new boards
2024-10-24 first boards manufactured
2024-11-05 first boards done, start of coding
2024-11-06 new vhdl code
2024-11-07 computer configs added, python script in progress
2024-11-09 doku. improved, python script in progress
2024-11-10 working ram upload
2024-11-10 working xsvf upload
2025-03-13 graphic updates
